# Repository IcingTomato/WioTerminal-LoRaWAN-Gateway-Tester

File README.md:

# WioTerminal LoRaWAN Gateway Tester for PlatformIO

## Introduction

The LoRaWAN Gateway Tester is a multipurpose portable tool that can detect the coverage of your LoRaWAN gateways. It will then apprise you of whether the signal is in a normal range. Designed to make the deployment of a LoRaWAN network easier, the LoRaWAN Gateway Tester will help you determine the optimum location for your LoRaWAN gateway deployment.

Prior to developing this, we checked out the LoRa tester market; the price usually ranges from $200 to $500, however, some of them lack a backend application to report the network signal, current time, status, and several other critical information. Therefore, we decided to bring a low-cost version ourselves that is able to do more! This project is based on [**Paul Pinault**](https://github.com/disk91/WioLoRaWANFieldTester)’s [**WioLoRaWANFieldTester**](https://www.disk91.com/2021/technology/lora/low-cost-lorawan-field-tester/) report. We are honoured to have access to his link and we thank him for his contributions. We combined Paul Pinault’s natty UI for the Wio terminal with LoRa-E5 and GNSS modules to produce the function of the LoRaWAN Gateway Tester.

<div align=center></div>

## Feature

- Menu selection for different modes of operation; Power controls, SF, test numbers input, etc.
- Supports various network segments (EU868, US915, US915HYBRID, AS923, KR920, IN865)
- Display LoRa device connection and uplink-downlink status
- Backup of previous test results
- Graphical display of RSSI and SNR
- Shows the number of uplink and downlink times, as well as the likelihood of packet loss
- GPS position reporting, as well as the current time and number of satellites.
- Display LoRa Device information i.e. DevEui, APPEui, Appkey, Firmware version, and more
- Define the DevEui, APPEui and Appkey

## Hardware 
The hardware used in this project is more affordable than most on the market, with the total cost adding up to less than a hundred dollars.

- [**WioTerminal**](https://www.seeedstudio.com/Wio-Terminal-p-4509.html)
- [**Wio Terminal Chassis - Battery (650mAh)**](https://www.seeedstudio.com/Wio-Terminal-Chassis-Battery-650mAh-p-4756.html)
- [**Wio Terminal Chassis - LoRa-E5 and GNSS**](https://www.seeedstudio.com/Wio-Terminal-p-4509.html)

## Usage

### Wio Terminal instruction

The LoRaWAN Gateway Tester basically sends a frame on-demand to the gateway on a regular basis, then transfers to the server (Uplink). It then waits for an ACK status. If the LoRa tester does not receive a response, it will continue to send the same frame until the preset number has been reached. The ACK, on the other hand, returns the response(Downlink) to the LoRa tester, implying that the message is forwarded to a backend service, from whence the information is eventually shown on the Wio terminal screen.
This project is based on the Arduino platform which means we’ll be using the Arduino IDE and various Arduino libraries. If this is your first time using the Wio terminal, here is a guide to quickly [**Get Started with Wio Terminal**](https://wiki.seeedstudio.com/Wio-Terminal-Getting-Started/).

requite library:
- [**Seeed_Arduino_SFUD**](https://github.com/Seeed-Studio/Seeed_Arduino_SFUD)
- [**TinyGPS**](https://github.com/mikalhart/TinyGPSPlus)
- [**LovyanGFX**](https://github.com/lovyan03/LovyanGFX)

### Note

When you upload the code, please selecte slave mode.
    <div align=center></div>

### TheThingsNetwork Console Configuration Setup

In this project, I test the LoRa tester on [**TheThingsNetwork**](https://www.thethingsnetwork.org) platform, the instuction as below:

Step 1: Load into [**TTN website**](https://www.thethingsnetwork.org) and create your account, then go to gateways start to set up your device.

<div align=center></div>

Step 2: Add the gateway device:
- Owner
- Gteway ID
- Gateway EUI
- Gateway name

<div align=center></div>

<div align=center></div>

<div align=center></div>

Step 3: Add Application:
- Owner
- Application ID
- Application name

<div align=center></div>

<div align=center></div>

Step 4：Add the LoRa node:
- Brand (Select Sense CAP)
- Model (Select LoRa-E5)
- Hardware Ver (Defult)
- Firmware Ver (Defult)
- Profile (The Region is according to your location)
- Frequency plan
- AppEUI
- DEVEUI
- AppKey
- End Device ID

<div align=center></div>

<div align=center></div>

Step 5: Add the code for decode the data:

<div align=center></div>

```CPP
function Decoder(bytes, port) {
 
  var decoded = {};
  if (port === 8) {
    decoded.latitude   = (bytes[3] | (bytes[2]<<8) | (bytes[1]<<16)  | (bytes[0]<<24)) /1000000;
    decoded.longitude  = (bytes[7] | (bytes[6]<<8) | (bytes[5]<<16)  | (bytes[4]<<24)) /1000000;
    decoded.altitude   = (bytes[9] | (bytes[8]<<8));
    decoded.satellites = bytes[9];
  }
 
  return decoded;
}
```

Step 5: Cheack the result on TheThingsNetwork

Go to the geteway, then click "Live data".

<div align=center></div>

### Wio terminal intruction

Each LoRa device has a unique serial number, after you connect the LoRa device to the Wio terminal then there will display the deveui, appeui and appkey on the first page, you need to fill the LoRa ID and gateway ID in server.

<div align=center></div>

There are Rssi and Snr data, and it will display the signal and Snr bar and packet loss after get the ACK respond.

<div align=center></div>

<div align=center></div>

This device have a GPS function as well, but it is not recommended for using in enclosed speace in case effect collect satellites.

<div align=center></div>

## schematic
Take a look at board directory for details on PCB & components.
Here is the simplified version of the schematics for DiY implementation.
if you want more detail, just go to check the file list.

<div align=center></div>

## Enclosure 

The 3D printed enclosure can be found in file list which is PCBA WioTerminal Chassis  H and PCB file. You will find the the all design on it. You will also find the FreeCad source file in case you want to modify /improve it.

The 3D prited work as below: 

<div align=center></div>

<div align=center></div>

<div align=center></div>

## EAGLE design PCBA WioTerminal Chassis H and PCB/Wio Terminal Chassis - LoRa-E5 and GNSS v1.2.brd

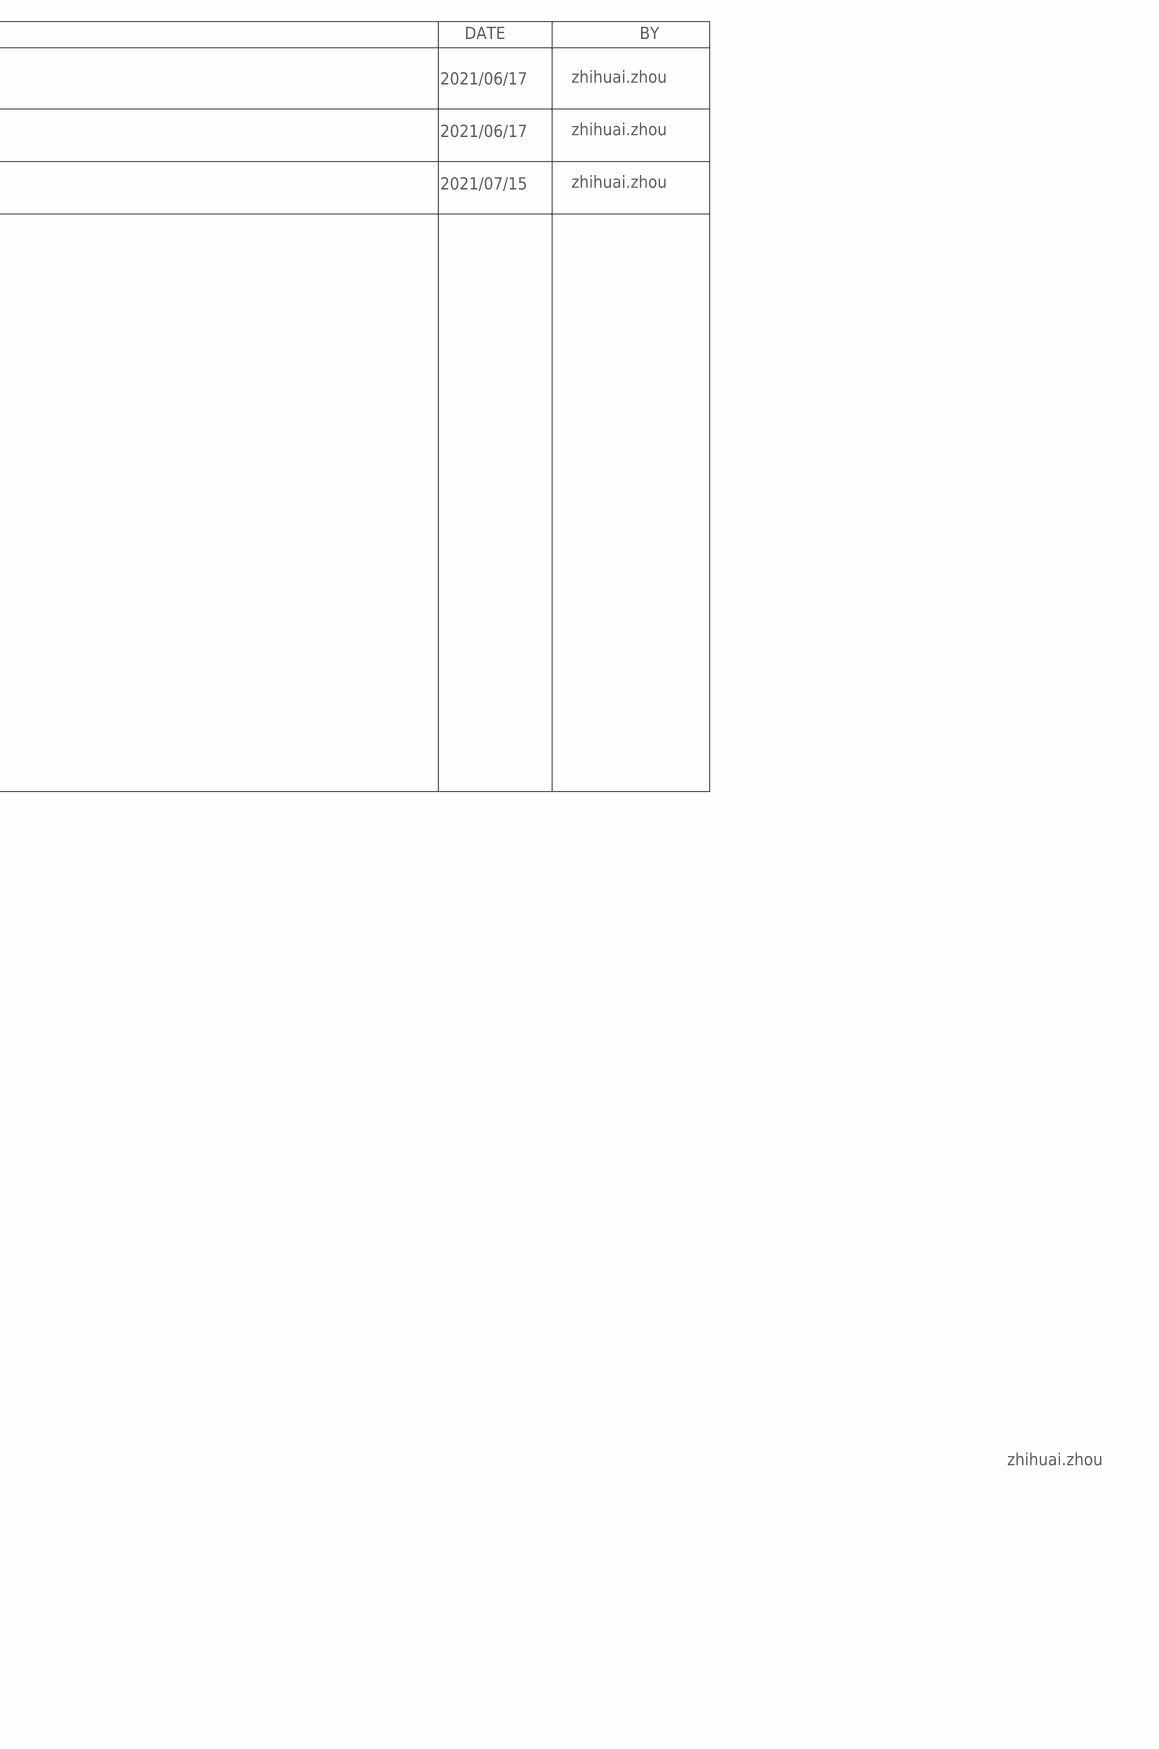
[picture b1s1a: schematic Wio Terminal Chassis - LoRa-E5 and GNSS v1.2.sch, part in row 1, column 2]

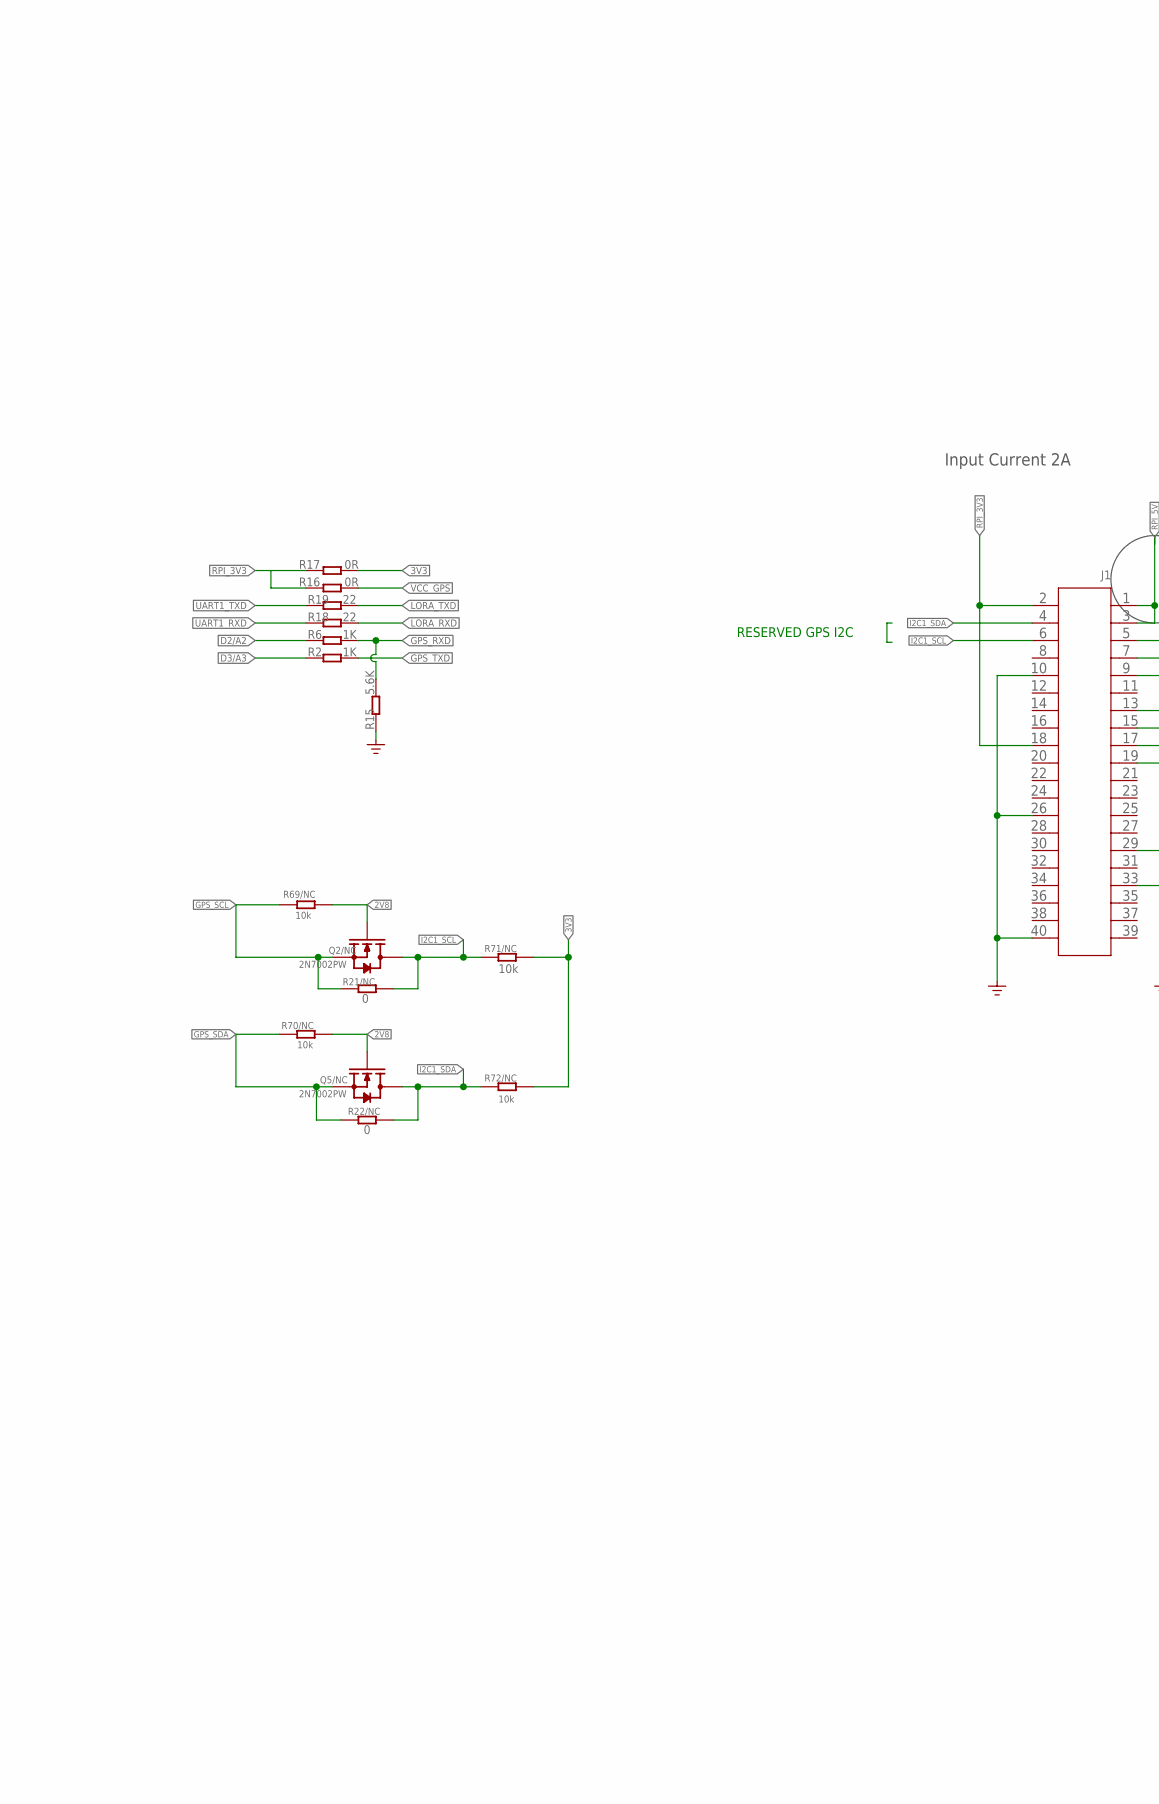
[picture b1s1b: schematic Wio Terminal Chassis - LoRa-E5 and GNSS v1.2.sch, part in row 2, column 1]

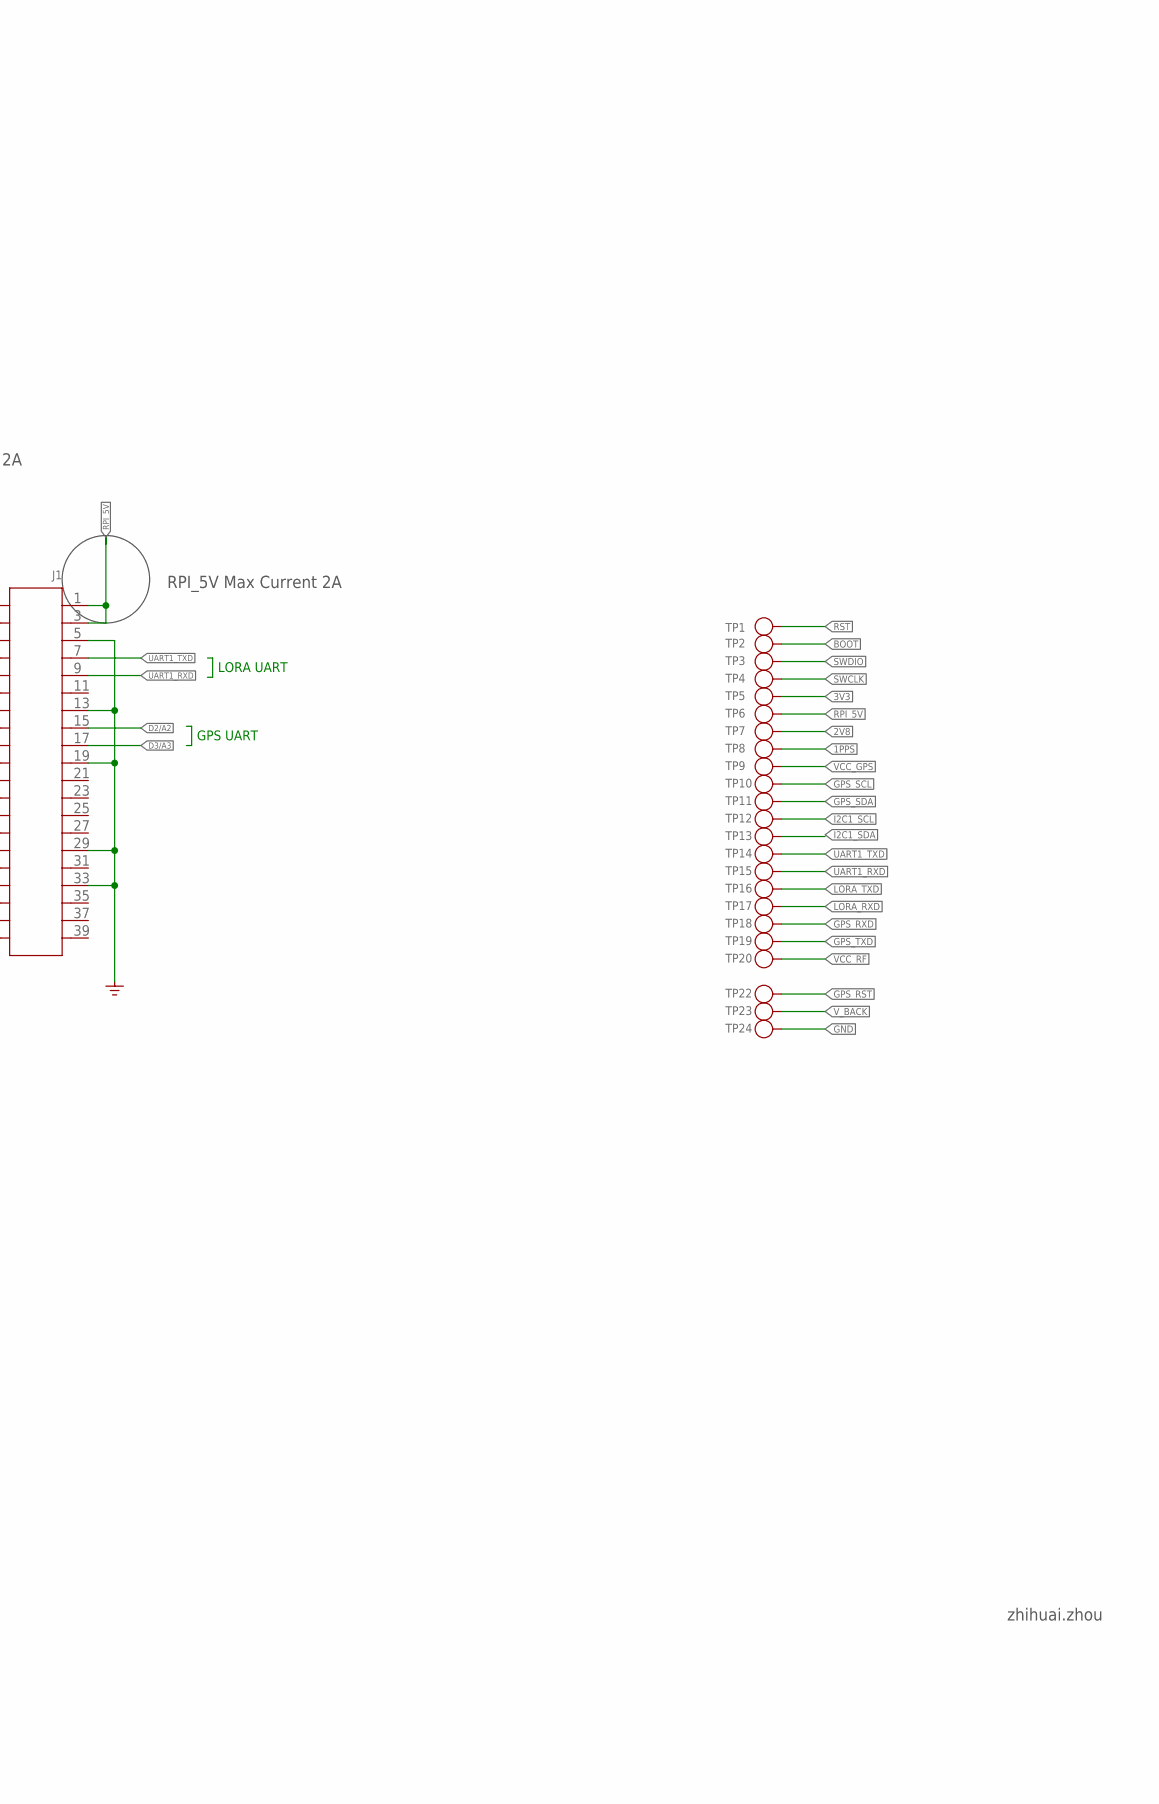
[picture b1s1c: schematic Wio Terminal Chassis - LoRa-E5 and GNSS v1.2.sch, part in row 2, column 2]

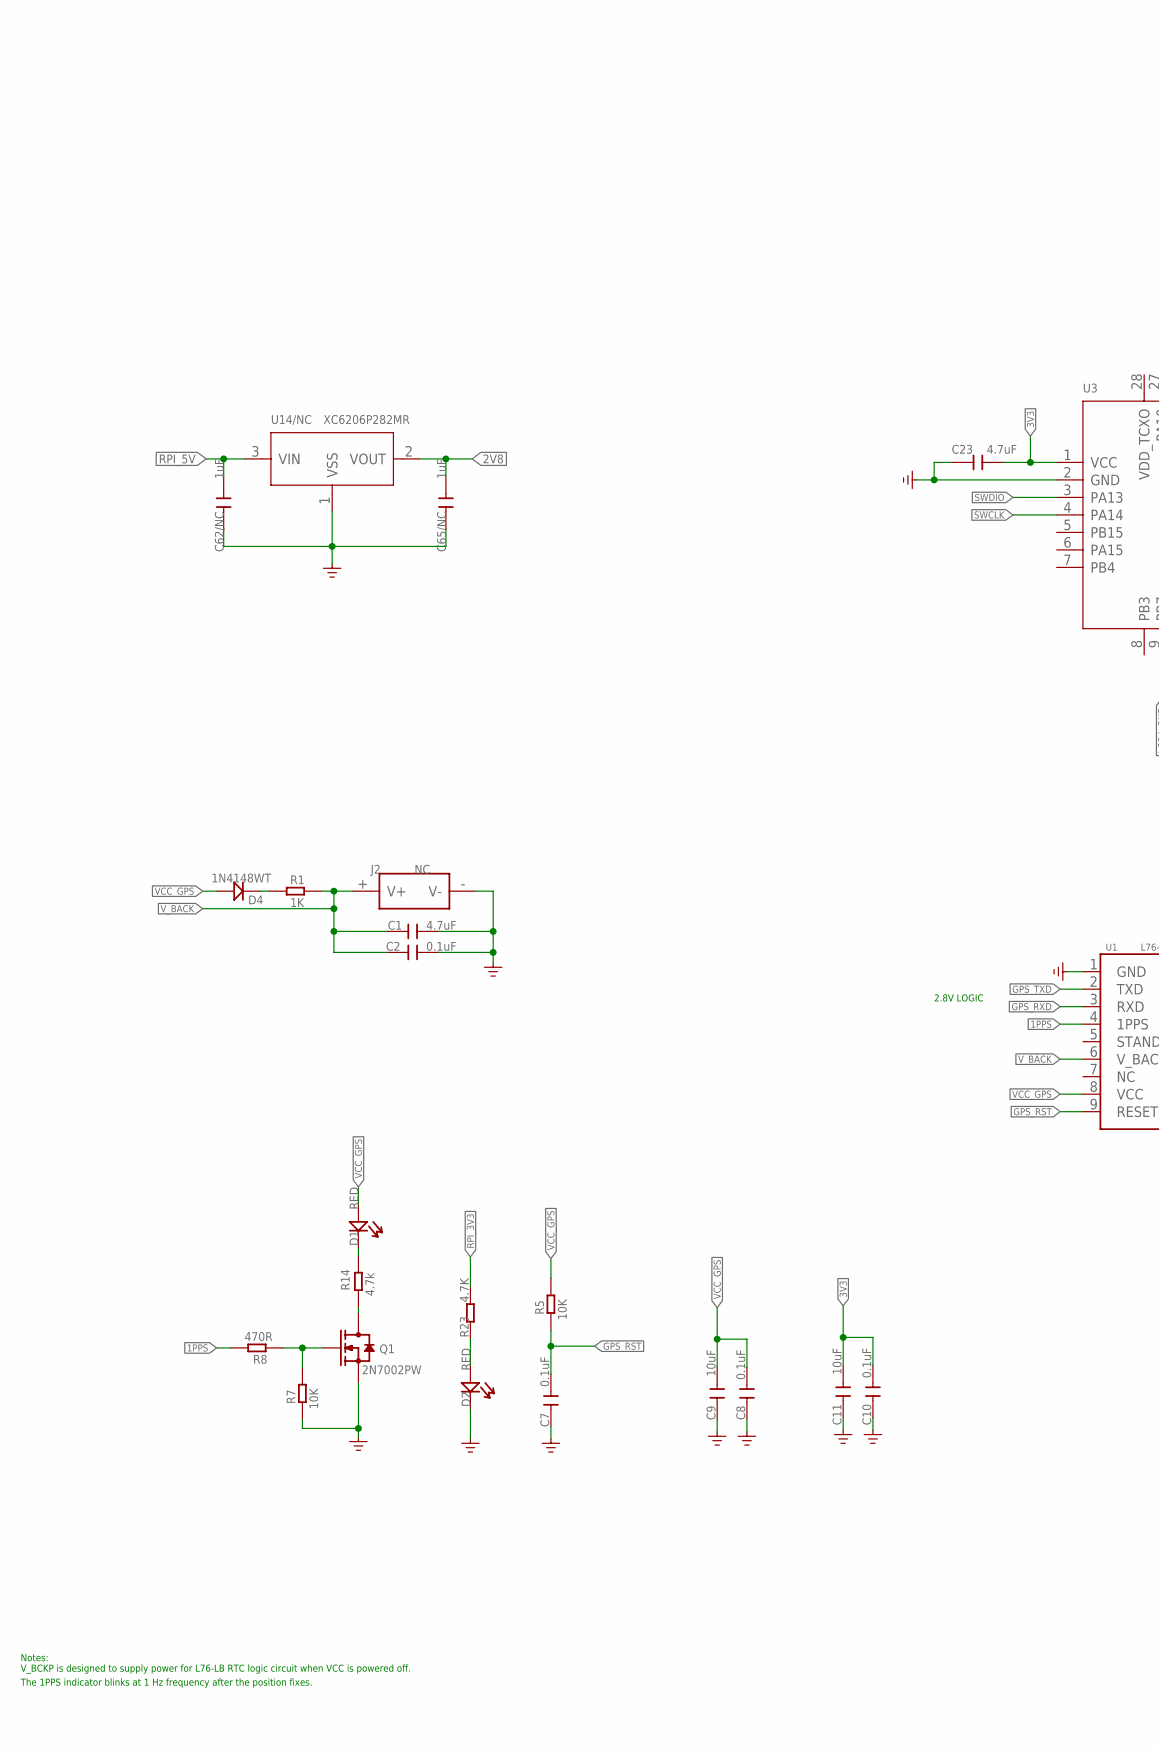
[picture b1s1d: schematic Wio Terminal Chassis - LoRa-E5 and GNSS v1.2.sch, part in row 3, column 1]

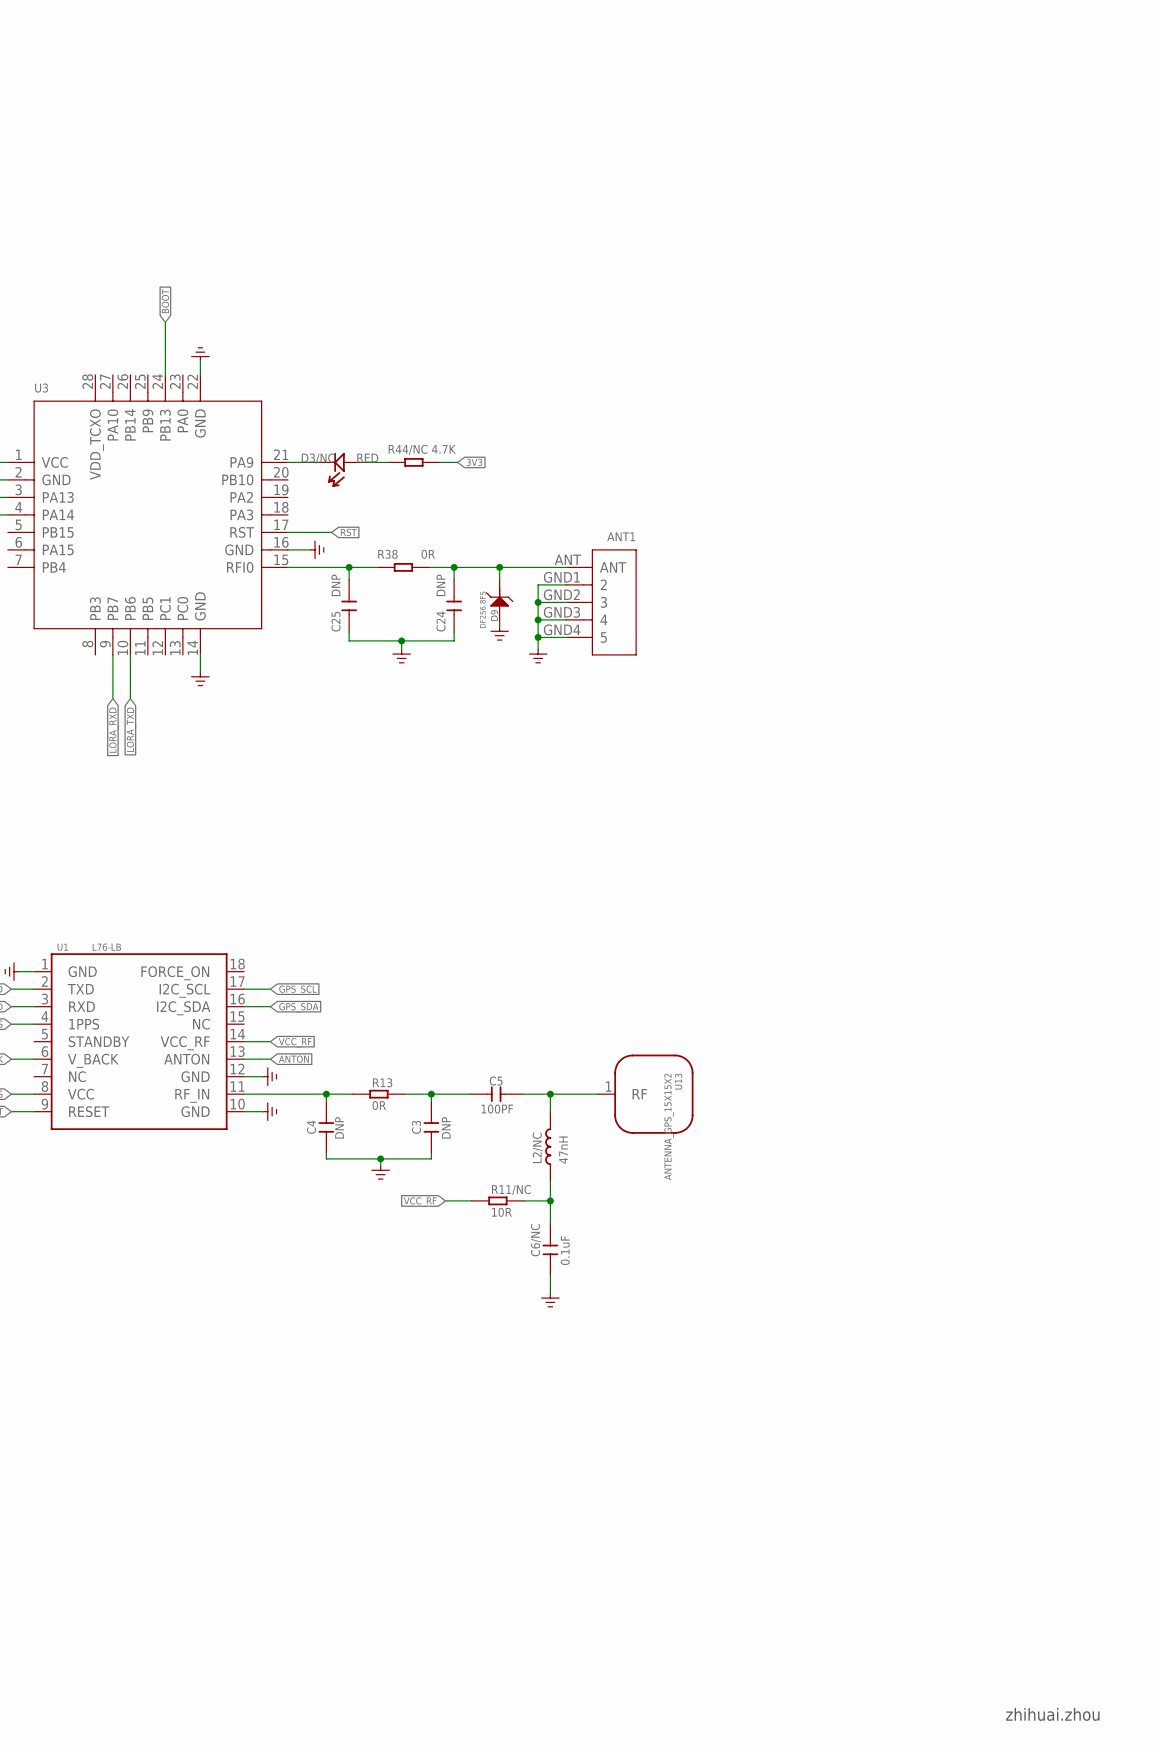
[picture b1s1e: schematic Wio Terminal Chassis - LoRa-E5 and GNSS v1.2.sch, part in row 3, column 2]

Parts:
ANT1: ANTENNA-SMA-MCX-JE-320160125; SMA5P-SMD-5.1-6.5X6.5X16.5MM
C1, C23: 4.7uF; C0603
C2, C6/NC, C7, C8, C10: 0.1uF; C0603
C3, C4, C24, C25: DNP; C0603
C5: 100PF; C0603
C9, C11: 10uF; C0603
C62/NC, C65/NC: 1uF; C0603
D1, D2, D3/NC: RED; LED-0603
D4: 1N4148WT; SOD-323
D9: DF2S6.8FS; SOD-923
J1: HEADER-2X20P-SMD-SMD; H2X20-SMD-2.54
J2: NC; SMD-CR1220-2
L2/NC: 47nH; L0603
Q1, Q2/NC, Q5/NC: 2N7002PW; SOT-23
R1, R2, R6: 1K; R0603
R5, R7: 10K; R0603
R8: 470R; R0603
R11/NC: 10R; R0603
R13, R16, R17, R38: 0R; R0603
R14: 4.7k; R0603
R15: 5.6K; R0603
R18, R19: 22; R0603
R21/NC, R22/NC: 0; R0603
R23, R44/NC: 4.7K; R0603
R69/NC, R70/NC, R71/NC, R72/NC: 10k; R0603
TP1, TP2, TP3, TP4, TP5, TP6, TP7, TP8, TP9, TP10, TP11, TP12, TP13, TP14, TP15, TP16, TP17, TP18, TP19, TP20, TP22, TP23, TP24: TEST; TP-D45MIL
U1: L76-LB; GPS_MODULE_L76-LB
U3: MOUDLE_LORA_E5; MOUDLE28P-1.25-12X12X2.5MM
U13: ANTENNA_GPS_15X15X2
U14/NC: XC6206P282MR; SOT-23

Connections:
1PPS: R8.2, TP8.T, U1.4 (1PPS)
2V8: C65/NC.1, Q2/NC.1 (G), Q5/NC.1 (G), R69/NC.2, R70/NC.2, TP7.T, U14/NC.2 (VOUT)
3V3: C10.1, C11.1, C23.2, R17.2, R44/NC.2, R71/NC.2, R72/NC.2, TP5.T, U3.1 (VCC)
ANTON: U1.13 (ANTON)
BOOT: TP2.T, U3.24 (PB13)
D2/A2: J1.15, R6.1
D3/A3: J1.17, R2.1
GND: ANT1.GND1 (2), ANT1.GND2 (3), ANT1.GND3 (4), ANT1.GND4 (5), C1.1, C2.1, C3.1, C4.1, C6/NC.1, C7.2, C8.2, C9.2, C10.2, C11.2, C23.1, C24.1, C25.1, C62/NC.2, C65/NC.2, D2.-, D9.2 (1), J1.5, J1.10, J1.13, J1.19, J1.26, J1.29, J1.33, J1.40, J2.- (V-), Q1.2 (S), R7.1, R15.1, TP24.T, U1.1 (GND), U1.10 (GND), U1.12 (GND), U3.2 (GND), U3.14 (GND), U3.16 (GND), U3.22 (GND), U14/NC.1 (VSS)
GPS_RST: C7.1, R5.1, TP22.T, U1.9 (RESET)
GPS_RXD: R6.2, R15.2, TP18.T, U1.3 (RXD)
GPS_SCL: Q2/NC.2 (S), R21/NC.1, R69/NC.1, TP10.T, U1.17 (I2C_SCL)
GPS_SDA: Q5/NC.2 (S), R22/NC.1, R70/NC.1, TP11.T, U1.16 (I2C_SDA)
GPS_TXD: R2.2, TP19.T, U1.2 (TXD)
I2C1_SCL: J1.6, Q2/NC.3 (D), R21/NC.2, R71/NC.1, TP12.T
I2C1_SDA: J1.4, Q5/NC.3 (D), R22/NC.2, R72/NC.1, TP13.T
LORA_RXD: R18.2, TP17.T, U3.9 (PB7)
LORA_TXD: R19.2, TP16.T, U3.10 (PB6)
unnamed: Q1.3 (D), R14.2
unnamed: Q1.1 (G), R7.2, R8.1
unnamed: D1.-, R14.1
unnamed: D4.-, R1.1
unnamed: C6/NC.2, L2/NC.1, R11/NC.2
unnamed: C4.2, R13.1, U1.11 (RF_IN)
unnamed: C5.2, L2/NC.2, U13.1
unnamed: C3.2, C5.1, R13.2
unnamed: D2.+, R23.1
unnamed: ANT1.ANT, C24.2, D9.1 (2), R38.2
unnamed: C25.2, R38.1, U3.15 (RFI0)
unnamed: D3/NC.+, R44/NC.1
unnamed: D3/NC.-, U3.21 (PA9)
RPI_3V3: J1.2, J1.18, R16.1, R17.1, R23.2
RPI_5V: C62/NC.1, J1.1, J1.3, TP6.T, U14/NC.3 (VIN)
RST: TP1.T, U3.17 (RST)
SWCLK: TP4.T, U3.4 (PA14)
SWDIO: TP3.T, U3.3 (PA13)
UART1_RXD: J1.9, R18.1, TP15.T
UART1_TXD: J1.7, R19.1, TP14.T
VCC_GPS: C8.1, C9.1, D1.+, D4.+, R5.2, R16.2, TP9.T, U1.8 (VCC)
VCC_RF: R11/NC.1, TP20.T, U1.14 (VCC_RF)
V_BACK: C1.2, C2.2, J2.+ (V+), R1.2, TP23.T, U1.6 (V_BACK)

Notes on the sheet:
Wio Terminal Chassis - LoRa-E5 and GNSS v1.0
2021/06/17
zhihuai.zhou
RPI_5V Max Current 2A
Input Current 2A
Notes: V_BCKP is designed to supply power for L76-LB RTC logic circuit when VCC is powered off.
The 1PPS indicator blinks at 1 Hz frequency after the position fixes.
2.8V LOGIC
LORA UART
GPS UART
RESERVED GPS I2C
Wio Terminal Chassis - LoRa-E5 and GNSS v1.1
Wio Terminal Chassis - LoRa-E5 and GNSS v1.2
2021/07/15

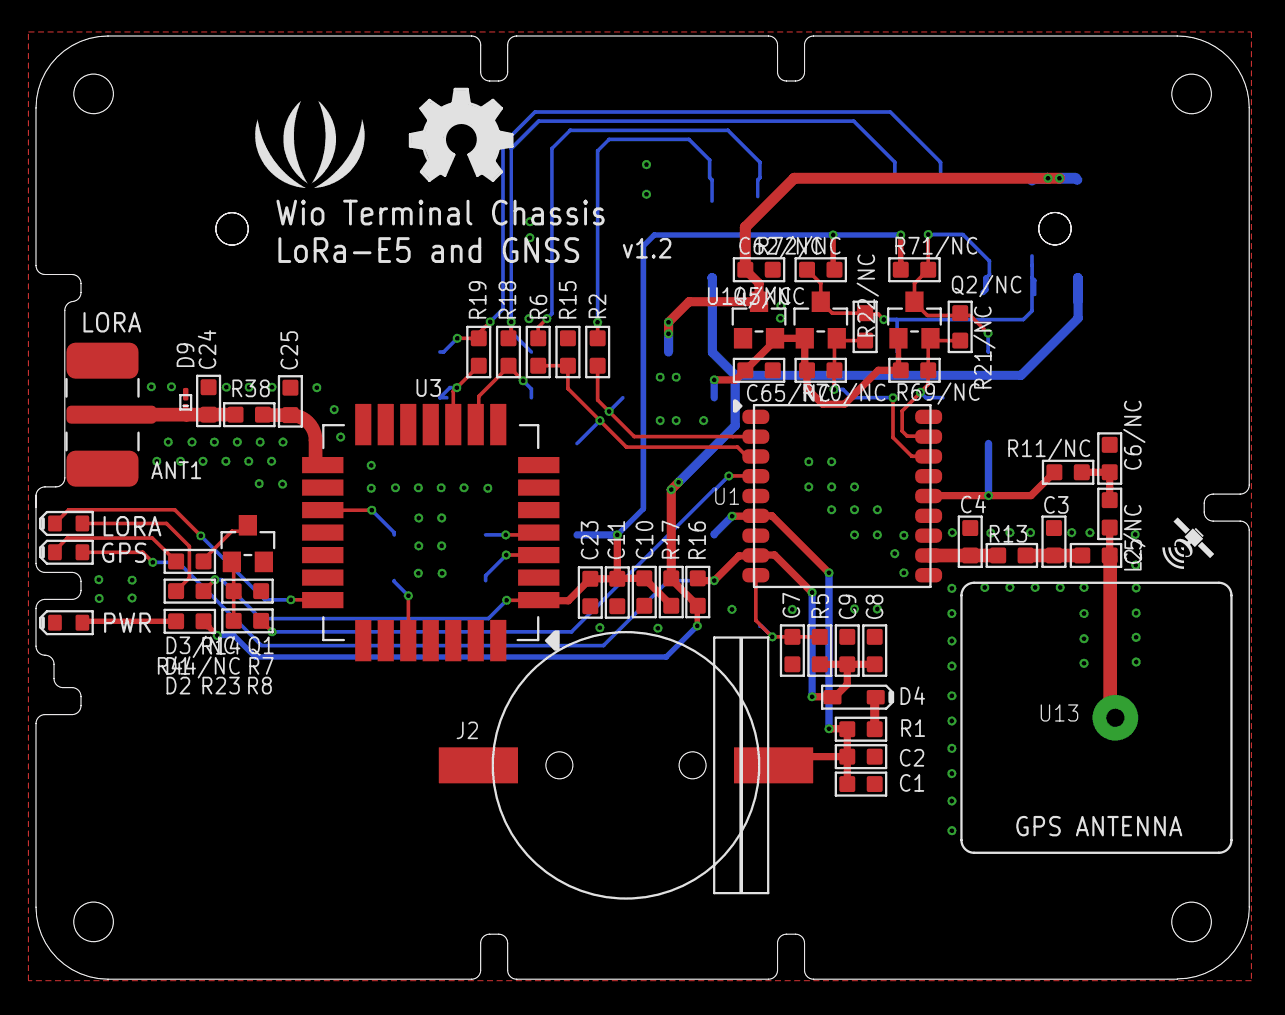
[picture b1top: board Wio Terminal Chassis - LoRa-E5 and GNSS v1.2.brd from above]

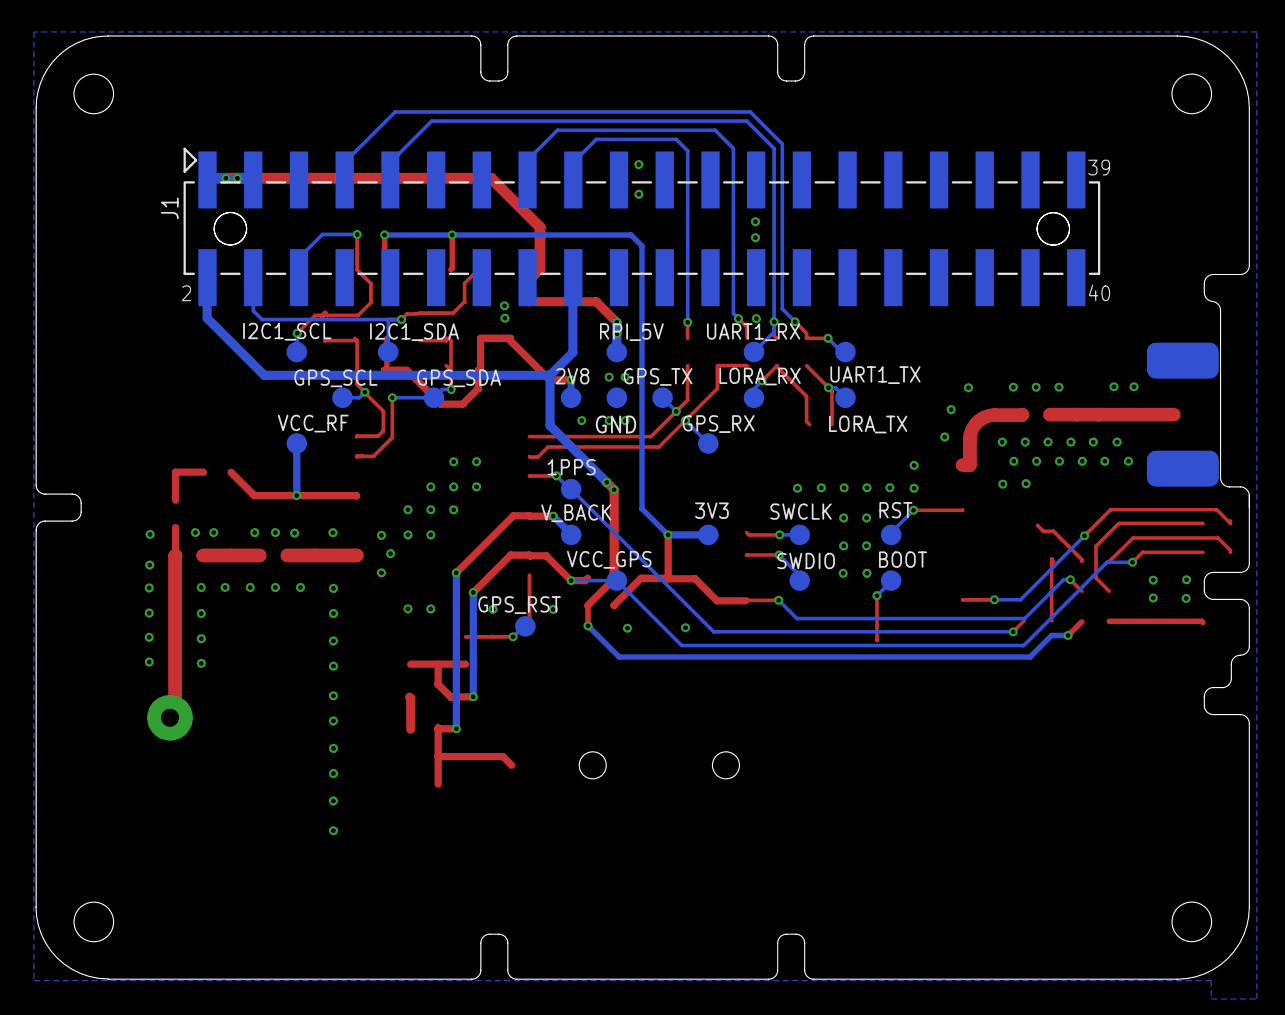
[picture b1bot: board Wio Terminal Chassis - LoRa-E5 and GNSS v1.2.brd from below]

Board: 2 copper layers, 67.4 x 52.4 mm, 80 parts (23 on the bottom side), 39 nets.

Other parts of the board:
U$16: OSHW_FILLX200_NOTEXT
U$17: LOGO_SILK

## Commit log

2021-06-25 add new project - LoRa gateway tester
2021-06-25 test upload git
2021-06-28 add readme centent
2021-06-28 changed the loading logo
2021-06-29 remove unless file
2021-07-01 1、Slove the problem of setting the transmit power an sf;2、Report GPS information
2021-07-09 fixed satallites can not display number
2021-07-16 1、add setting Region;2、remove some debug infomation;
2021-07-16 optimize the library
2021-07-23 1、AT Command timeout to reinitialize the radio;2、Update UI interface call library；3、Allow setting US915 SF=12;4、The Gps altitude information is only two bytes accurate to the meter;5、SNR and RSSI onl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
2021-07-23 add SoftwareSerial1 file，set the _receive_buffer to 1200 bytes
2021-07-26 1、Optimize LoRa Module code;2、increase setting DevEui、AppEui、AppKey
2021-07-27 1、not support AU915;2、fix abnormal gps information;3、display RSSI information by default;4、Restrict US915 to set DR0
2021-07-29 fixed the network segment slelction
2021-07-29 add pic and UI contributor
2021-07-29 add new feature
2021-07-30 add H&PCB and new content on readme
2021-07-30 add 3D work pic
2021-08-05 Delete: Delete all files
2021-08-05 Update: Update PlatformIO
2021-08-05 Update: Update LICENSE
2021-08-05 Update LICENSE

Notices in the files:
parts and their libraries:
moudle-new: CC-BY-SA
